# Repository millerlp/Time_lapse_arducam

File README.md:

# Timelapse_ArduCam

This repository contains Arduino code and Eagle design files for a circuit board to interface
with an ArduCam camera module to generate timelapse images. The device will sleep until a 
user defined interval (some number of seconds) is reached, then it will boot up the 
ArduCam module, take one picture, and write it to the SD card before returning to sleep. The
ArduCam module consumes > 100mA while idling, so the AVR microcontroller uses a transistor to
cut off all power to the ArduCam, and puts itself to sleep as well. During sleep intervals the
average overall current draw of the entire device is < 1mA. During an image capture and save 
routine (approx 5-6 seconds), power draw is around 130mA. 

The price for parts and the PCB boards should come out to $75, including the $30 cost of 
of the ArduCam OV2640 2 megapixel camera module
[Amazon link to camera module,](https://www.amazon.com/Arducam-Module-Megapixels-Arduino-Mega2560/dp/B012UXNDOY)
(note that the 5 megapixel version ought to work on this board as well) and the $22 cost to get 3 copies of the circuit board made by OshPark.com
[direct link to this board on Osh Park](https://oshpark.com/shared_projects/j0asS2vJ)

Features:
* Images are stored on a micro SD card.
* Timekeeping is accomplished with a DS3231 real time clock chip and backup battery.
* Power is provided by batteries through one of the available power plugs, either a 2.1mm barrel
connector or JST PH series plug (similar to that used on many Lithium battery packs). A 3.3V 
low dropout voltage regulator is included. I typically use 4 AA batteries to power the unit.
* A reset button and a trigger button are included, and can be mounted on either top or bottom 
of the board. 
* Indicator LEDs may also be mounted on the top or bottom of the board. 
* A FTDI header allows reprogramming of the AVR atmega328P microcontroller.
* A standard ICSP 2x3 header is available for burning a bootloader to the AVR. Alternatively, 
a Tag-Connect TC2030 footprint is available for ICSP functions as well. 

Necessary libraries:
* Arducam: https://github.com/ArduCAM/Arduino
* SdFat: https://github.com/greiman/SdFat
* RTClib: https://github.com/millerlp/RTClib

Written under Arduino 1.6.6

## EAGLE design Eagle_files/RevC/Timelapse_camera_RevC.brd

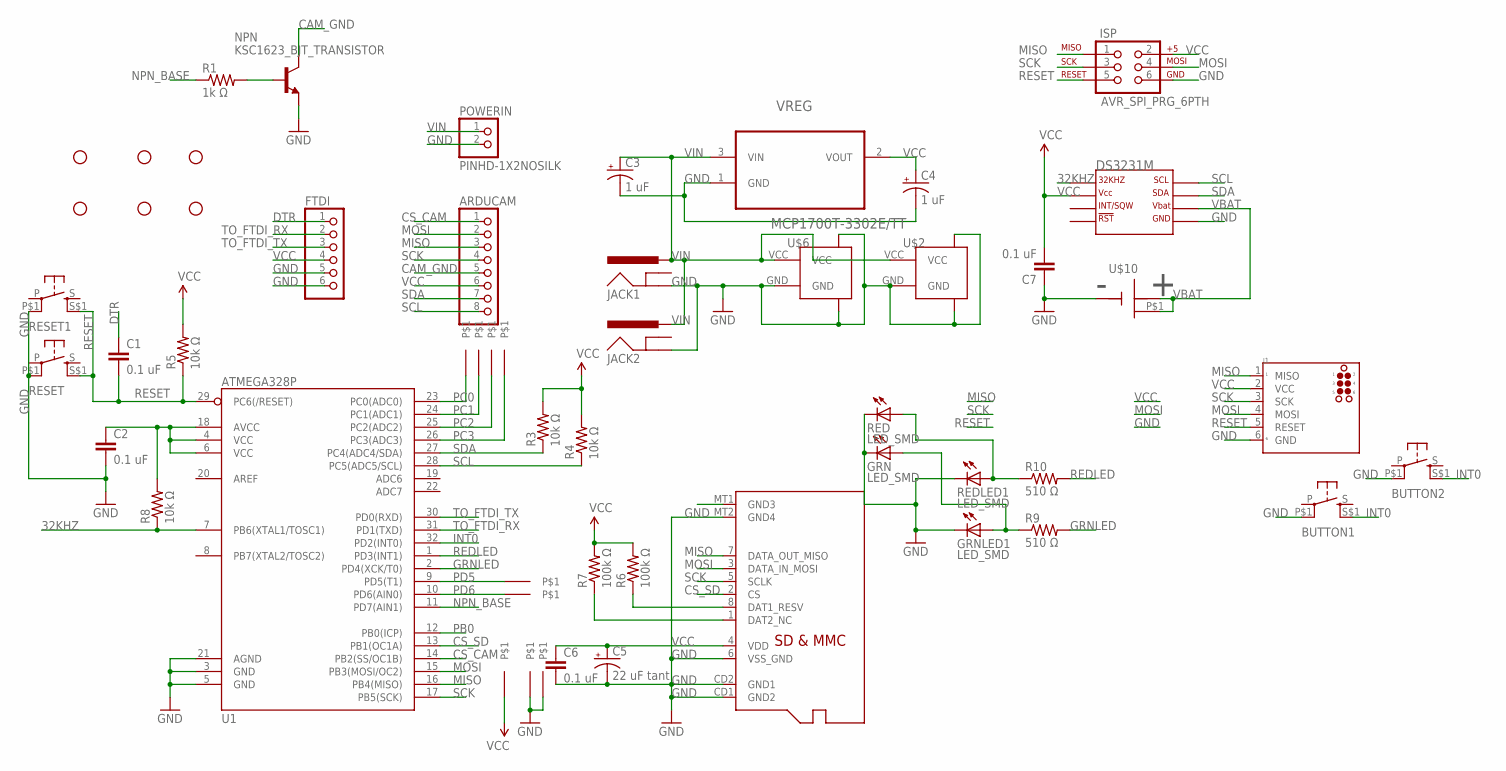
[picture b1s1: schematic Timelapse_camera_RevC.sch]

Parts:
ARDUCAM: PINHD-1X8RIGHTANGLE_FEMALE; 1X08-RA
BUTTON1, BUTTON2: PUSHBUTTON_DPST_SMDSTANDARD; PUSHBUTTON_DPST_SMD
C1, C2, C6, C7: 0.1 uF; 0805
C3, C4: 1 uF; PANASONIC_B
C5: 22 uF tant; C0805_POL
DS3231M: DS3231MSOIC-8; DS3231M_SOIC8
FTDI: PINHD-1X6CB; 1X06-CLEANBIG
GRN: LED_SMD; CHIPLED_0805
GRNLED1: LED_SMD; CHIPLED_0805
ISP: AVR_SPI_PRG_6PTH; 2X3
J1: TC2030-MCP-NL
JACK1, JACK2: POWER_JACK_2,1MM; POWER_JACK_DC_2,1MM
NPN: KSC1623_BJT_TRANSISTOR; SOT23
POWERIN: PINHD-1X2NOSILK; 1X02_NOSILK
R1: 1k Ω; R0805
R3, R4, R5, R8: 10k Ω; R0805
R6, R7: 100k Ω; R0805
R9, R10: 510 Ω; R0805
RED: LED_SMD; CHIPLED_0805
REDLED1: LED_SMD; CHIPLED_0805
RESET, RESET1: PUSHBUTTON_DPST_SMDSTANDARD; PUSHBUTTON_DPST_SMD
STANDOFF1, STANDOFF2, STANDOFF3, STANDOFF4, STANDOFF5, STANDOFF6: STAND-OFF
U1: ATMEGA328P; TQFP32-08
U$1, U$4, U$7, U$8, U$9, U$11, U$12, U$13, U$14: PINHD-1X1STANDARD; 1X01
U$2, U$6: JST-2PIN; JST-2-SMD-VERT
U$3: MICROSD
U$10: BATTERY_BUTTON_CELLCR1220_SMD; CR1220_BATTERY_HOLDER_SMD
VREG: MCP1700T-3302E/TT; SOT95P237X112-3N

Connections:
32KHZ: DS3231M.1 (P$1_32KHZ), R8.1, U1.7 (PB6(XTAL1/TOSC1))
CAM_GND: ARDUCAM.5, NPN.3 (C)
CD1: U$3.MT1 (GND3)
CS_CAM: ARDUCAM.1, U1.14 (PB2(SS/OC1B))
CS_SD: U1.13 (PB1(OC1A)), U$3.2 (CS)
DTR: C1.1, FTDI.1
GND: BUTTON1.P$1 (P1), BUTTON2.P$1 (P1), C2.2, C3.-, C4.-, C5.P$2_C (-), C6.2, C7.1, DS3231M.5 (P$5_GND), FTDI.5, FTDI.6, GRN.C, GRNLED1.C, ISP.6, J1.6 (GND), JACK1.P$2 (GND), JACK2.P$2 (GND), NPN.2 (E), POWERIN.2, RED.C, REDLED1.C, RESET.P$1 (P1), RESET1.P$1 (P1), U1.3 (GND), U1.5 (GND), U1.21 (AGND), U$2.GND, U$2.P$1 (BODY1), U$2.P$2 (BODY2), U$3.6 (VSS_GND), U$3.CD1 (GND2), U$3.CD2 (GND1), U$3.MT2 (GND4), U$6.GND, U$6.P$1 (BODY1), U$6.P$2 (BODY2), U$10.GND, U$12.1, U$14.1, VREG.1 (GND)
GRNLED: R9.2, U1.2 (PD4(XCK/T0))
INT0: BUTTON1.S$1 (S1), BUTTON2.S$1 (S1), U1.32 (PD2(INT0))
MISO: ARDUCAM.3, ISP.1, J1.1 (MISO), U1.16 (PB4(MISO)), U$3.7 (DATA_OUT_MISO)
MOSI: ARDUCAM.2, ISP.4, J1.4 (MOSI), U1.15 (PB3(MOSI/OC2)), U$3.3 (DATA_IN_MOSI)
unnamed: NPN.1 (B), R1.2
unnamed: R7.1, U$3.1 (DAT2_NC)
unnamed: R6.1, U$3.8 (DAT1_RESV)
unnamed: GRN.A, GRNLED1.A, R9.1
unnamed: R10.1, RED.A, REDLED1.A
NPN_BASE: R1.1, U1.11 (PD7(AIN1))
PB0: U1.12 (PB0(ICP))
PC0: U1.23 (PC0(ADC0)), U$1.1
PC1: U1.24 (PC1(ADC1)), U$4.1
PC2: U1.25 (PC2(ADC2)), U$7.1
PC3: U1.26 (PC3(ADC3)), U$8.1
PD5: U1.9 (PD5(T1)), U$9.1
PD6: U1.10 (PD6(AIN0)), U$11.1
REDLED: R10.2, U1.1 (PD3(INT1))
RESET: C1.2, ISP.5, J1.5 (RESET), R5.1, RESET.S$1 (S1), RESET1.S$1 (S1), U1.29 (PC6(/RESET))
SCK: ARDUCAM.4, ISP.3, J1.3 (SCK), U1.17 (PB5(SCK)), U$3.5 (SCLK)
SCL: ARDUCAM.8, DS3231M.8 (P$8_SCL), R4.1, U1.28 (PC5(ADC5/SCL))
SDA: ARDUCAM.7, DS3231M.7 (P$7_SDA), R3.1, U1.27 (PC4(ADC4/SDA))
TO_FTDI_RX: FTDI.2, U1.31 (PD1(TXD))
TO_FTDI_TX: FTDI.3, U1.30 (PD0(RXD))
VBAT: DS3231M.6 (P$6_VBAT), U$10.P$1 (P$2_VBAT), U$10.P$2 (VBAT)
VCC: ARDUCAM.6, C2.1, C4.+, C5.P$1_A (+), C6.1, C7.2, DS3231M.2 (P$2_VCC), FTDI.4, ISP.2, J1.2 (VCC), R3.2, R4.2, R5.2, R6.2, R7.2, R8.2, U1.4 (VCC), U1.6 (VCC), U1.18 (AVCC), U$3.4 (VDD), U$13.1, VREG.2 (VOUT)
VIN: C3.+, JACK1.P$1 (PWR), JACK2.P$1 (PWR), POWERIN.1, U$2.VCC, U$6.VCC, VREG.3 (VIN)

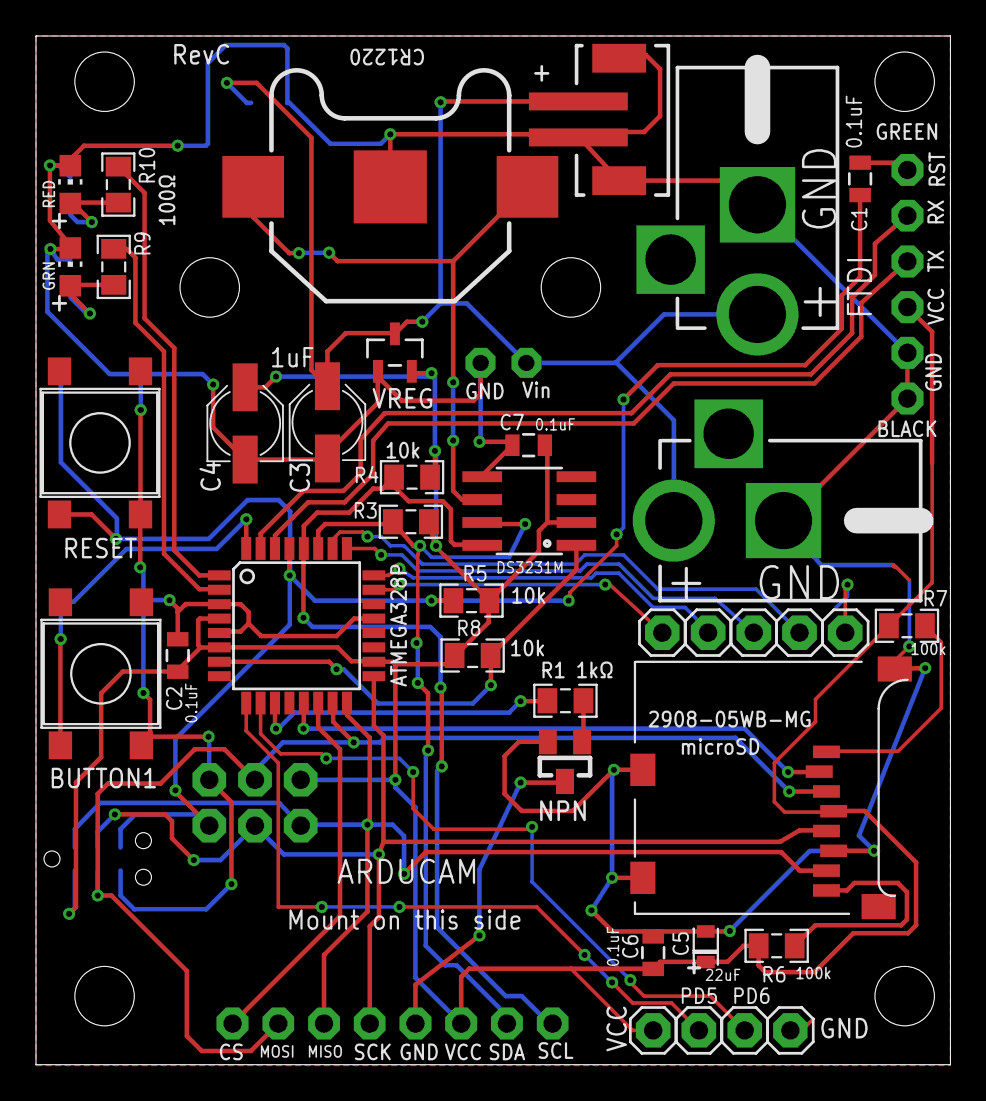
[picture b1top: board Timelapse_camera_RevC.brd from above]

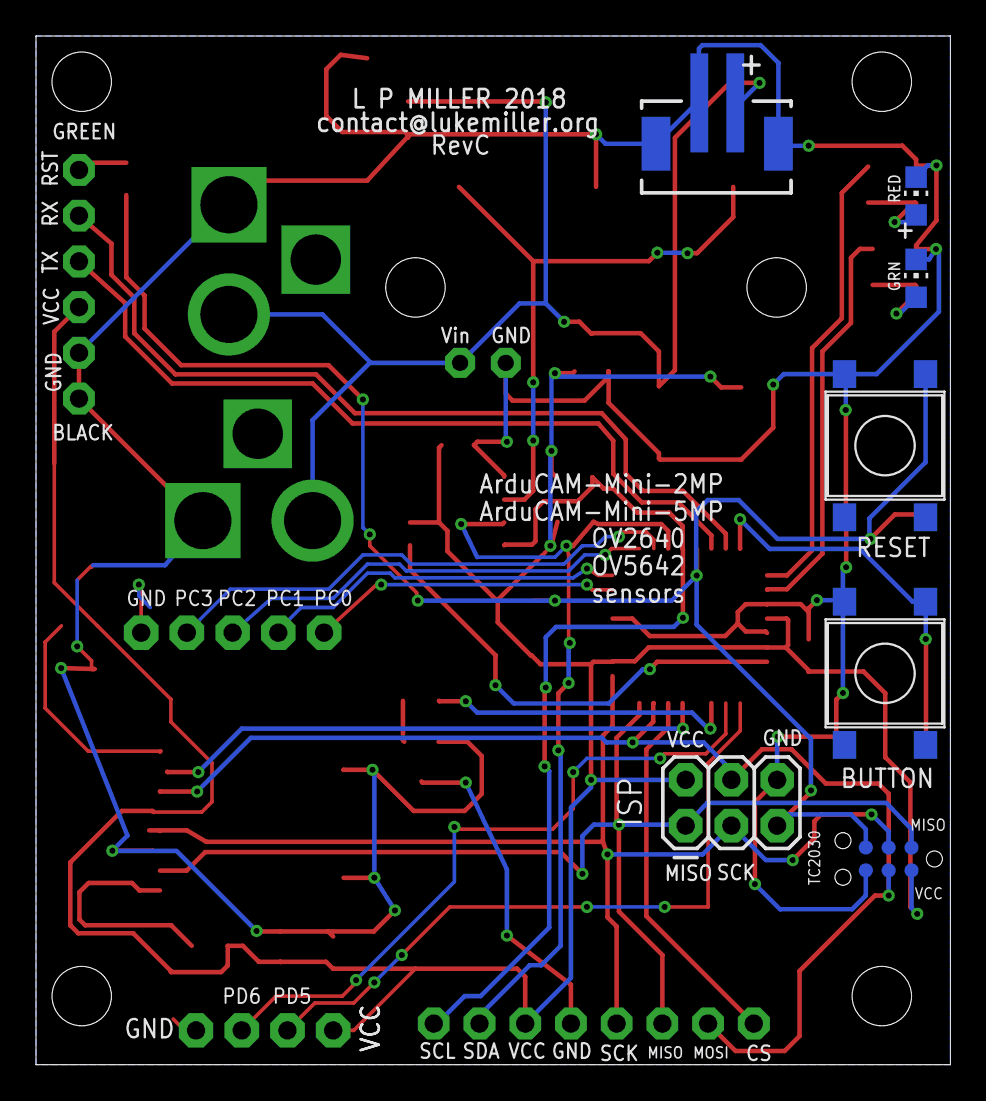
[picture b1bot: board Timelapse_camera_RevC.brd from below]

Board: 2 copper layers, 50.8 x 57.1 mm, 54 parts (8 on the bottom side), 32 nets.

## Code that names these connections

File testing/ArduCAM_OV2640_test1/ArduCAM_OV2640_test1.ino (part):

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#endif

// Define the CS pin for the SD card 
#define SD_CS 9    // arduino pin 9, avr pin PB1
#define SPI_CS 10  // arduino pin 10, avr pin PB2
#define GRNLED PD4
#define REDLED PD3
#define BUTTON1 2
#define NPN PD7

// set pin 10 as the slave select for SPI:
//const int SPI_CS = 10;
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//**************************************
void setup()
{
  pinMode(GRNLED, OUTPUT);
  pinMode(REDLED, OUTPUT);
  pinMode(SPI_CS, OUTPUT);
  pinMode(NPN, OUTPUT);
  digitalWrite(NPN, HIGH);
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
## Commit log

2016-06-14 :confetti_ball: Added .gitattributes & .gitignore files
2016-06-15 Updating for RevA camera board hardware
2016-06-16 Functional on RevA hardware, but power hungry
2016-07-03 Enabling basic functionality with RevB hardware
    This works with the RevB board, but only proves that the thing takes a
    picture. No real low power sleeping happens.
2016-07-03 Semi-functional status, does not fully power down
    This will take pictures on command on RevB hardware, but turning off the
    power to the Arducam via the NPN transistor appears to kill the I2C
    communications as well, which is weird.
2016-07-03 All SPI/I2C pins as inputs, seems to still loop properly
    Need to see if the Arducam is truly being powered down though, or if
    it's still getting parasitic power from somewhere.
2016-07-03 Functional test, sleep mode power down works
    Camera current is dropping to < 1mA when the Arducam power is cut off.
    Pressing button1 wakes the camera and successfully takes a picture (at
    120-140mA current draw) for 3-4 seconds, then resumes sleeping.
2016-07-03 Added automatic interval picture code, working
    New version takes a picture automatically at the specified time
    interval, and retains the manual trigger option as well. Tested working
    on battery power, sleeping at <1mA between pictures.
2016-07-03 Removing some cruft code.
2016-07-03 Cleaning up, adding comments.
2016-07-03 Adding readme file
2016-07-03 Adding Eagle PCB design files
2016-07-03 Image of assembled Revision B circuit board
2016-07-03 Initial commit of main working program
2016-07-03 Adding image
2016-07-03 Adding clock time check
2016-07-03 More commentary added
2016-07-03 More commentary
2016-07-03 Adding parts list
2016-07-03 Adding costs
2016-07-03 fixing
2016-07-03 Removed image
2016-07-03 Details details
2016-07-03 Fixing link
2016-07-03 Tweaking some more text
2016-07-04 Updating circuit board link
2016-07-04 Adding info
2016-07-04 Editing
2016-07-04 Altered reboot LED signal to just use green
    Also using green led instead of red to indicate picture taking (at the
    delay)
2016-07-07 Adding successful bootup quick flash
    Green will flash on reboot, and if the camera and SD card both
    initialize then a 2nd faster green flash will occur before the main loop
    starts.
2016-07-08 Still non-functional, something is adding random bytes to the start of each subsequent JPEG file after the first successful image is saved.
2016-07-09 Writing clean JPEG files now, after removing static int
    In the writeToSD function there was a variable declaration static int i
    = 0; This appears to have been preserving the i value between function
    calls (separate image-to-SD write events), and so adding some of the
    previous image's data to the start of the current image, making a
    semi-corrupted jpeg. Changing i to a standard int instead of static int
    appears to have fixed this.
2016-07-09 Setting reboot flashes, cleaning functions
    Adding comments and user guide in preamble. Cleaning up + formatting
    comments.
2016-07-22 Fixing all the stuff the merge broke
2016-07-22 Created a boards.txt entry for Arduino
2018-05-06 Moving Rev B to its own folder
2018-05-06 Creating RevC with GPIO breakouts

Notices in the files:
testing/ArduCAM_OV2640_test1/ArduCAM_OV2640_test1.ino:
ArduCAM demo (C)2014 Lee
parts and their libraries:
miller: ©2009 ROFA.cz - modified and updated by Robert Darlington ‹rdarlington@gmail.com›
